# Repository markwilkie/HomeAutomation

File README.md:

# HomeAutomation
Arduino, Raspberry Pi, and Windows Azure code for RF based home automation

Arduino sketches use the library from http://tmrh20.github.io/RF24/ 

RPi config file reader from http://www.hyperrealm.com/libconfig/

Github is here, but it didn't compile for me:  https://github.com/hyperrealm/libconfig

To compile config file reader:
- Copy, then unzip the libary onto your Pi
- CD into the directory and type 'sh ./configure --disable-cxx'
- make
- sudo make install
- 
Random Notes:
- To increase your nrf24 range:  http://chelnyshops.ru/enhanced-nrf24l01-radio-with-a-diy-dipole-antenna/

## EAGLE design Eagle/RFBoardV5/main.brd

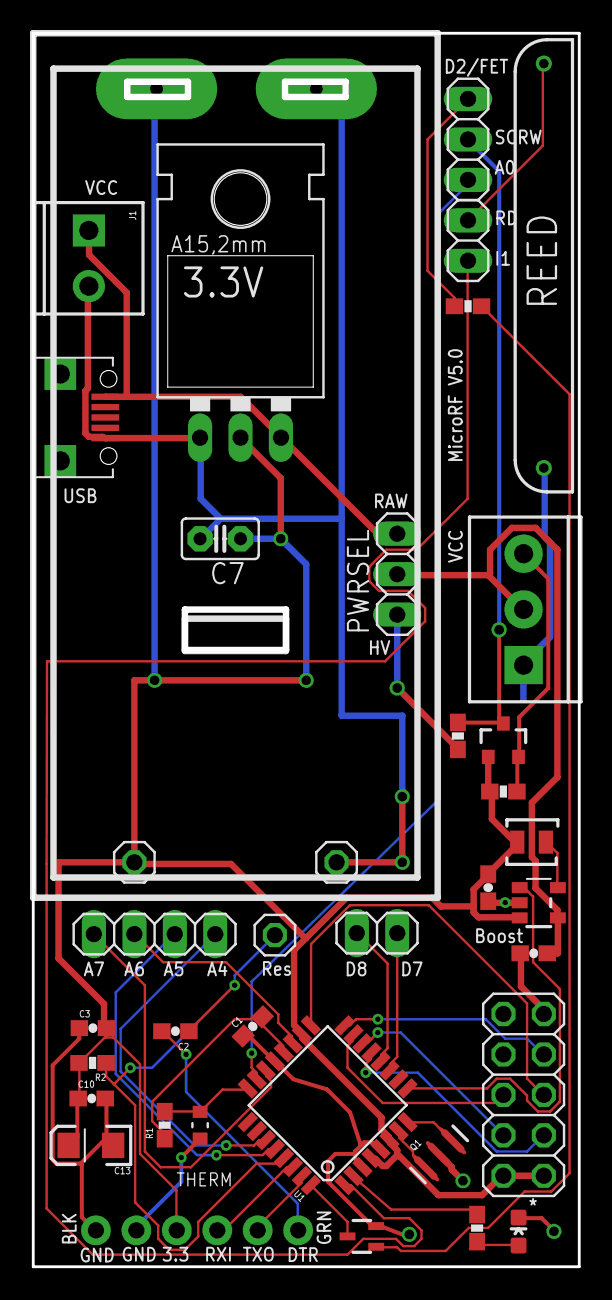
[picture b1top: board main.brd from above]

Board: 2 copper layers, 34.3 x 77.5 mm, 38 parts (1 on the bottom side), 36 nets.

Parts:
3.3V: LD117V33; TO220L1
A0___D2: 1X03
BST: XC9140; SOT23-5
C1, C2, C3, C10: 0.1uF; 0603-CAP
C4: 10uF; 0603-CAP
C5: 4.7uF; 0603-CAP
C7: C2.5-2
C13: 10uF; EIA3216
D3: Green; 0603-LED-ALT1
D7-D1, D7-D8: 1X02
GND: 1X01
J1: SCREWTERMINAL-3.5MM-2
JP1: FTDI Basic; 1X06
JP2: USB-RECEPTABLE; FCI-10103594-0001LF
JP3: 1X04
JP4: SCREWTERMINAL-3.5MM-3
JP5: 2X05
JP6: 1X01
L1: VLF302512MT
PWRSEL: 1X03
Q1: 8/16/20MHz; RESONATOR-SMD-1:1
Q2: BSS138; SOT23-3
R1: 10K 1%; 0603-RES
R2, R3, R4, R5: 10K; 0603-RES
R6: 330; 0603-RES
S3: REED-SWITCH-MK6-10; MK6-10
T1: SOT323
THERM: 10K Ohms; RESC1608X95N
U1: ATMEGA328; TQFP32-08
U$1: BAT; AAABATTERY
VCC(3.3): 1X01

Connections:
3.3V: 3.3V.2, BST.3, C3.2, C5.2, C7.1, C10.1, C13.A, JP1.4, JP5.1, JP5.2, L1.1, Q2.1, R2.2, R4.1, U1.4, U1.6, U1.18, U$1.VCC, VCC(3.3).1
A0: A0___D2.3, U1.23
A1: R1.2, THERM.1, U1.24
A4: JP3.4, U1.27
A5: JP3.3, U1.28
A6: JP3.2, U1.19
A7: JP3.1, U1.22
AREF: C1.2, R1.1, U1.20
BOOST_VCC: BST.4, C4.2, JP4.2, PWRSEL.2
CE: JP5.3, U1.13
CSN: JP5.4, U1.14
D2_INT0: T1.1, U1.32
D2_VIA_FET: A0___D2.1, R3.2
D3_INT1: D7-D1.2, U1.1
D5: BST.1, U1.9
D7: D7-D8.2, U1.11
D8: D7-D8.1, U1.12
DTR: C2.2, JP1.1
GND: 3.3V.1, BST.2, C1.1, C3.1, C4.1, C5.1, C7.2, C10.2, C13.C, D3.C, GND.1, J1.2, JP1.5, JP1.6, JP2.5, JP4.1, JP5.9, JP5.10, Q1.2, S3.2, T1.3, THERM.2, U1.3, U1.5, U1.21, U$1.GND
HV: PWRSEL.1, R5.1
HV_SIG1: A0___D2.2, Q2.3, R5.2
LED/D4: R6.1, U1.2
MISO: JP5.7, U1.16
MOSI: JP5.6, U1.15
unnamed: Q1.3, U1.8
unnamed: Q1.1, U1.7
unnamed: R3.1, T1.2
unnamed: D3.A, R6.2
unnamed: BST.5, L1.2
RAW_PWR: 3.3V.3, J1.1, JP2.1, PWRSEL.3
REED: D7-D1.1, S3.1
RESET: C2.1, JP6.1, R2.1, U1.29
RXI: JP1.3, U1.30
SCK: JP5.5, U1.17
SCREW_TERM: JP4.3, Q2.2, R4.2
TXO: JP1.2, U1.31

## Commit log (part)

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2026-01-25 quick path fix
2026-01-25 fixed bt2 detail
2026-01-25 warning --> info logging
2026-01-25 removing noise
2026-01-25 updated intervals for checking tanks etc
2026-01-26 disconnect retry improvments
2026-01-27 Removed ble/wifi off/on for tank reads
    turns out the conflicts was not real
2026-01-27 improved logging and cleaned up days/hours left formatting
2026-01-27 cosmetic on days left for tanks
2026-01-27 formatting
2026-01-28 stale display cosmetic updates
2026-02-03 shows last values when in backoff (offline)
2026-02-06 fixed gauge behavior when battery offline & calibrated water tank
2026-02-18 added gps + tracker and elevation calibrator
    - upgraded to 3.3.7 arduino core
    - added gps support
    - added auto barameter calibration using topo lookup
    - uploading track to traccor
    - removed OTA support to save flash space
2026-02-18 file refactor
2026-02-19 traccar works now
2026-02-19 using real time now from gps and hiding secrets
2026-02-24 switched GPS, fixed ldr and ign blocking calls
2026-02-25 barameter changed to non-blocking oneshot
2026-03-10 GPS w/ elevation check now works
2026-03-20 won't end trip until I've actually left
2026-04-04 comprehensive car search
2026-04-05 fix wind speed, eeprom layout, remove time reset on new trip
2026-04-06 update readme with setup instructions and library table
2026-04-08 fix pitot i2c errors, stagger sensor reads, fix boost gauge on startup
2026-04-08 add pitot diagnostic logging to papertrail
2026-04-10 Add MQTT broker location (Synology NAS) to README
2026-05-28 Document MQTT auth behavior and SmartThings MQTT driver hang note
2026-06-23 Initial minisplit commit
2026-06-25 Added blind6, and created a way to generate new blind info w/ no capture
2026-06-25 Latest updates
2026-06-25 updated docs
2026-06-26 more docs
2026-06-30 UNTESTED - added bme280

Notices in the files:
parts and their libraries:
SparkFun-Connectors: Licensing: Creative Commons ShareAlike 4.0 International - https://creativecommons.org/licenses/by-sa/4.0
inductor-tdk: Copyright (C) 2008, Bob Starr
